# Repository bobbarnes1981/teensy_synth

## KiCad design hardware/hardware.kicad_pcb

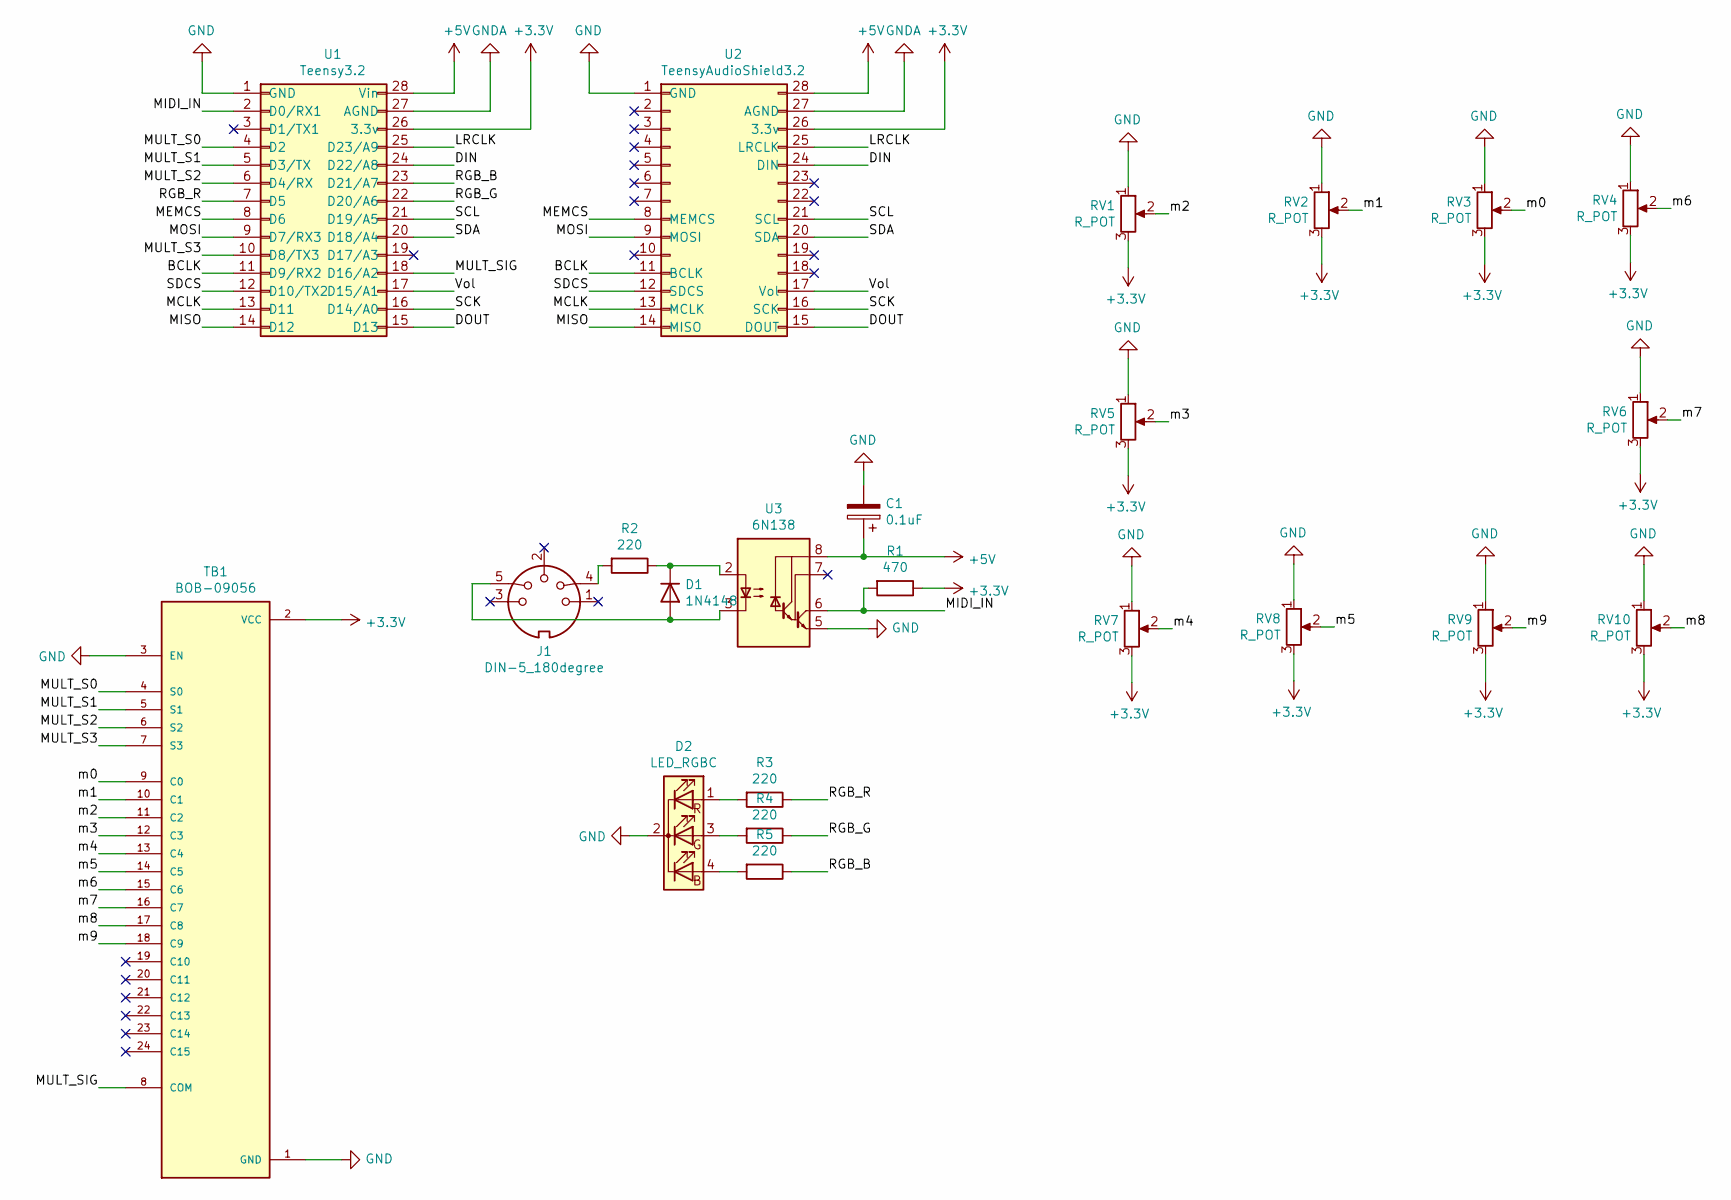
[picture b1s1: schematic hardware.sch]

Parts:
C1: 0.1uF; C_Rect_L7.0mm_W2.5mm_P5.00mm
D1: 1N4148; D_DO-35_SOD27_P10.16mm_Horizontal
D2: LED_RGBC; LED_D5.0mm-4_RGB
J1: DIN-5_180degree; PinHeader_1x05_P2.54mm_Vertical
R1: 470; R_Axial_DIN0207_L6.3mm_D2.5mm_P10.16mm_Horizontal
R2, R3, R4, R5: 220; R_Axial_DIN0207_L6.3mm_D2.5mm_P10.16mm_Horizontal
RV1, RV2, RV3, RV4, RV5, RV6, RV7, RV8, RV9, RV10: R_POT; Potentiometer_Alpha_RD901F-40-00D_Single_Vertical_CircularH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
TB1: BOB-09056; XDCR_BOB-09056; PARTREV N/A
U1: Teensy3.2
U2: TeensyAudioShield3.2; TeensyArduinoShield3.2
U3: 6N138; DIP-8_W7.62mm_Socket_LongPads

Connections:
+3V3: R1.1, RV1.3, RV2.3, RV3.3, RV4.3, RV5.3, RV6.3, RV7.3, RV8.3, RV9.3, RV10.3, TB1.2 (VCC), U1.26 (3.3v), U2.26 (3.3v)
+5V: C1.1, U1.28 (Vin), U2.28, U3.8 (VCC)
/BCLK: U1.11 (D9/RX2), U2.11 (BCLK)
/DIN: U1.24 (D22/A8), U2.24 (DIN)
/DOUT: U1.15 (D13), U2.15 (DOUT)
/LRCLK: U1.25 (D23/A9), U2.25 (LRCLK)
/MCLK: U1.13 (D11), U2.13 (MCLK)
/MEMCS: U1.8 (D6), U2.8 (MEMCS)
/MIDI_IN: R1.2, U1.2 (D0/RX1), U3.6 (VO2)
/MISO: U1.14 (D12), U2.14 (MISO)
/MOSI: U1.9 (D7/RX3), U2.9 (MOSI)
/MULT_S0: TB1.4 (S0), U1.4 (D2)
/MULT_S1: TB1.5 (S1), U1.5 (D3/TX)
/MULT_S2: TB1.6 (S2), U1.6 (D4/RX)
/MULT_S3: TB1.7 (S3), U1.10 (D8/TX3)
/MULT_SIG: TB1.8 (COM), U1.18 (D16/A2)
/RGB_B: R5.1, U1.23 (D21/A7)
/RGB_G: R4.1, U1.22 (D20/A6)
/RGB_R: R3.1, U1.7 (D5)
/SCK: U1.16 (D14/A0), U2.16 (SCK)
/SCL: U1.21 (D19/A5), U2.21 (SCL)
/SDA: U1.20 (D18/A4), U2.20 (SDA)
/SDCS: U1.12 (D10/TX2), U2.12 (SDCS)
/Vol: U1.17 (D15/A1), U2.17 (Vol)
/m0: RV3.2, TB1.9 (C0)
/m1: RV2.2, TB1.10 (C1)
/m2: RV1.2, TB1.11 (C2)
/m3: RV5.2, TB1.12 (C3)
/m4: RV7.2, TB1.13 (C4)
/m5: RV8.2, TB1.14 (C5)
/m6: RV4.2, TB1.15 (C6)
/m7: RV6.2, TB1.16 (C7)
/m8: RV10.2, TB1.17 (C8)
/m9: RV9.2, TB1.18 (C9)
GND: C1.2, D2.2 (K), RV1.1, RV2.1, RV3.1, RV4.1, RV5.1, RV6.1, RV7.1, RV8.1, RV9.1, RV10.1, TB1.1 (GND), TB1.3 (EN), U1.1 (GND), U2.1 (GND), U3.5 (GND)
GNDA: U1.27 (AGND), U2.27 (AGND)
unnamed: D1.1 (K), R2.1, U3.2 (C1)
unnamed: D1.2 (A), J1.5, U3.3 (C2)
unnamed: D2.1 (RA), R3.2
unnamed: D2.3 (GA), R4.2
unnamed: D2.4 (BA), R5.2
unnamed: J1.4, R2.2

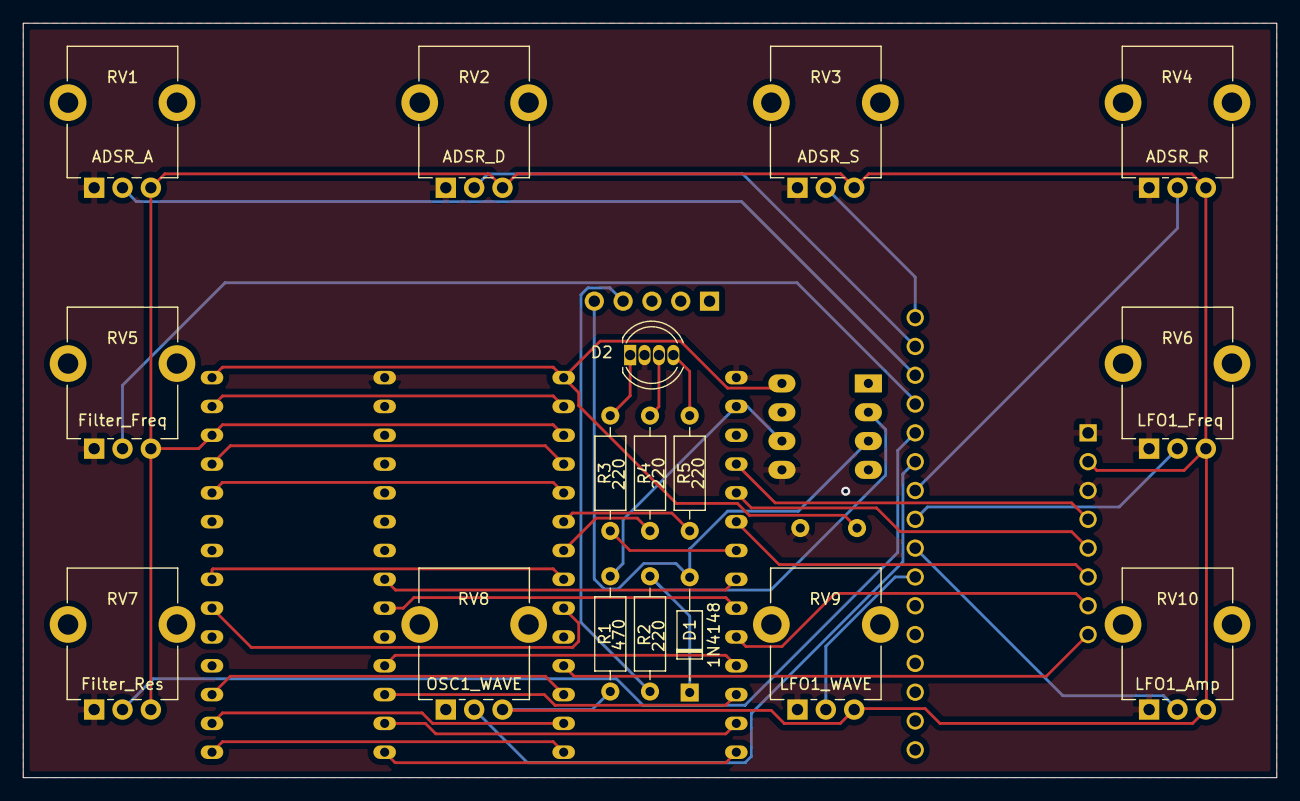
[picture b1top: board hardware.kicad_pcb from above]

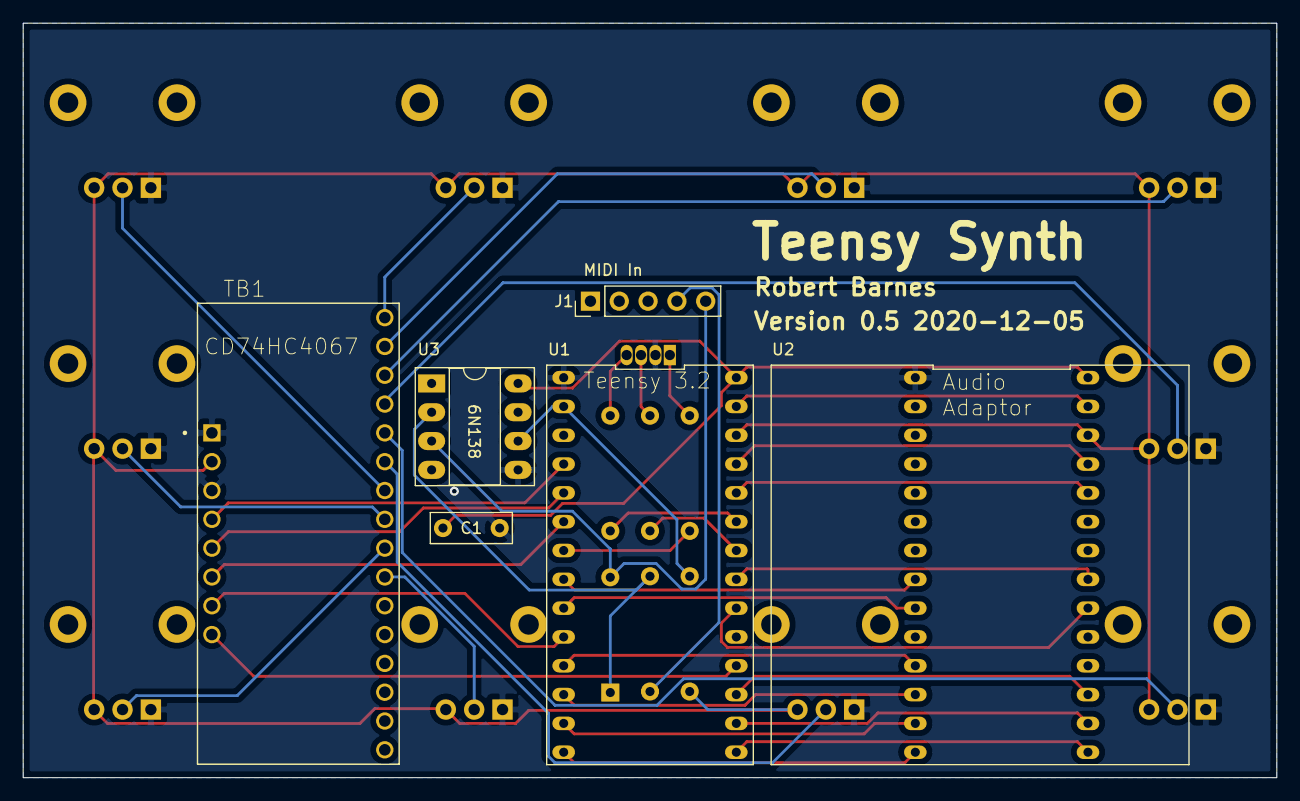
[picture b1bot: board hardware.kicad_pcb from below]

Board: 2 copper layers, 110.5 x 66.5 mm, 23 parts (6 on the bottom side), 42 nets.

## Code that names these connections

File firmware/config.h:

#ifndef _CONFIG_H
#define _CONFIG_H

#define PCB_0V5

//#define USE_USBMIDI
#define USE_MIDI

#define LED 13

#define NOTE_MIN 23
#define NOTE_MAX 108

#define LFO_FREQ_MAX 50

#define FILTER_FREQ_MAX 10000
#define FILTER_RES_MIN 0.7
#define FILTER_RES_MAX 5.0

#define ADSR_ATTACK_MAX 3000
#define ADSR_DECAY_MAX 3000
#define ADSR_RELEASE_MAX 3000

#define MULTIPLEX_MAX 0x09
#define MULTIPLEX_S0 2
#define MULTIPLEX_S1 3
#define MULTIPLEX_S2 4
#if defined(PCB_0V3) || defined(PCB_0V4) 
#define MULTIPLEX_S3 5
#endif
#if defined(PCB_0V5)
#define MULTIPLEX_S3 8
#endif
#define MULTIPLEX_IN A2
#define MULTIPLEX_MICROS 1000
#define MULTIPLEX_CHANGE 5

#define CC_OSC1_WAVE 102
#define CC_FILTER_FREQ 103
#define CC_FILTER_RES 104
#define CC_ADSR_A 105
#define CC_ADSR_D 106
#define CC_ADSR_S 107
#define CC_ADSR_R 108
#define CC_LFO1_WAVE 109
#define CC_LFO1_AMP 110
#define CC_LFO1_FREQ 111

#define CC_CHANNEL_ALLSOUNDOFF 120
#define CC_CHANNEL_RESETALLCONTROLLERS 121
#define CC_CHANNEL_LOCALCONTROL 122
#define CC_CHANNEL_ALLNOTESOFF 123

#if defined(PCB_0V3) || defined(PCB_0V4) 
#define MUX_FILTER_FREQ 0
#define MUX_FILTER_RES 1
#define MUX_ADSR_A 2
#define MUX_ADSR_D 3
#define MUX_ADSR_S 4
#define MUX_ADSR_R 5
#define MUX_OSC1_WAVE 6
#define MUX_LFO1_AMP 7
#define MUX_LFO1_FREQ 8
#define MUX_LFO1_WAVE 9
#endif
#if defined(PCB_0V5)
#define MUX_FILTER_FREQ 3
#define MUX_FILTER_RES 4
#define MUX_ADSR_A 2
#define MUX_ADSR_D 1
#define MUX_ADSR_S 0
#define MUX_ADSR_R 6
#define MUX_OSC1_WAVE 5
#define MUX_LFO1_AMP 8
#define MUX_LFO1_FREQ 7
#define MUX_LFO1_WAVE 9
#endif

#define RGB_R 5
#define RGB_G 20
#define RGB_B 21

#endif

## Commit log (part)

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2020-11-17 Rename kicad project
2020-11-17 Add custom symbols/footprints for teensy and audio board
2020-11-17 Add midi connector footprint
2020-11-17 Prototype layout for pcb
2020-11-18 Add some buttons and pots
2020-11-20 Schematic changes
2020-11-20 Generate waveform and modify
2020-11-20 Add waveforms and pure-data control over midi
2020-11-20 Lesson 3 - start/stop notes, keybuffer
2020-11-21 Lesson 4 - add ADSR and cleanup controls in PD
2020-11-21 Lesson 6 - detune second osc and select osc waveforms
2020-11-21 Lesson 6 - add filter
2020-11-21 Add bit crusher
2020-11-21 Lesson 7 add pitch bend
2020-11-21 Add midi hardware I/O
2020-11-22 Simplify and customise
2020-11-22 Add multiplexer and update pcb
2020-11-22 Layout pcb
2020-11-23 Tidy control interface
2020-11-23 Move controls to unused numbers
2020-11-24 Update references
2020-11-24 Update footprints
2020-11-24 Add image of kicad 2d model
2020-11-25 Add LFO
2020-11-25 Add extra controls, convert pcb to use connectors
2020-11-27 Remove reference to rescue library
2020-11-27 Add panel idea
2020-11-29 Add multiplexer code and midi control channel messages
2020-11-30 Add 6n138 and pull down resistors to schematic
2020-11-30 Add pull-downs to pcb
2020-12-02 Add noise channel
2020-12-03 Remove MIDI out and add RGB LED header
2020-12-03 Move RGB_R and MULT address pins to get RGB on PWM pin
2020-12-04 Enable local control
2020-12-04 Use old pin numbers for old pcb
2020-12-04 Implement wav buttons
2020-12-04 Change amount of analog change to ignore
2020-12-04 Add conditions for other pcb versions
2020-12-05 V0.5 PCB for Hammond case with pcb mount pots
2020-12-05 Redesign board to allow space for connectors
2020-12-05 Add text to silks
2020-12-05 Remove panel, add measurements to PCB
2020-12-06 Change MIDI Out label to MIDI In
2020-12-18 Switch to 0v5 config
2020-12-19 Resize controls
2020-12-19 Update images
2020-12-19 Make footprint match LED pinout even if schematic looks wrong
2020-12-19 Add test code for LED
2020-12-19 Just flash rgb colours untill we decide what the LED should indicate
2020-12-19 Move defines to config.h
2020-12-19 Force values to be read at startup
2020-12-20 Enable midi connection
2021-01-05 Use correct schematic diagram for RGB led
